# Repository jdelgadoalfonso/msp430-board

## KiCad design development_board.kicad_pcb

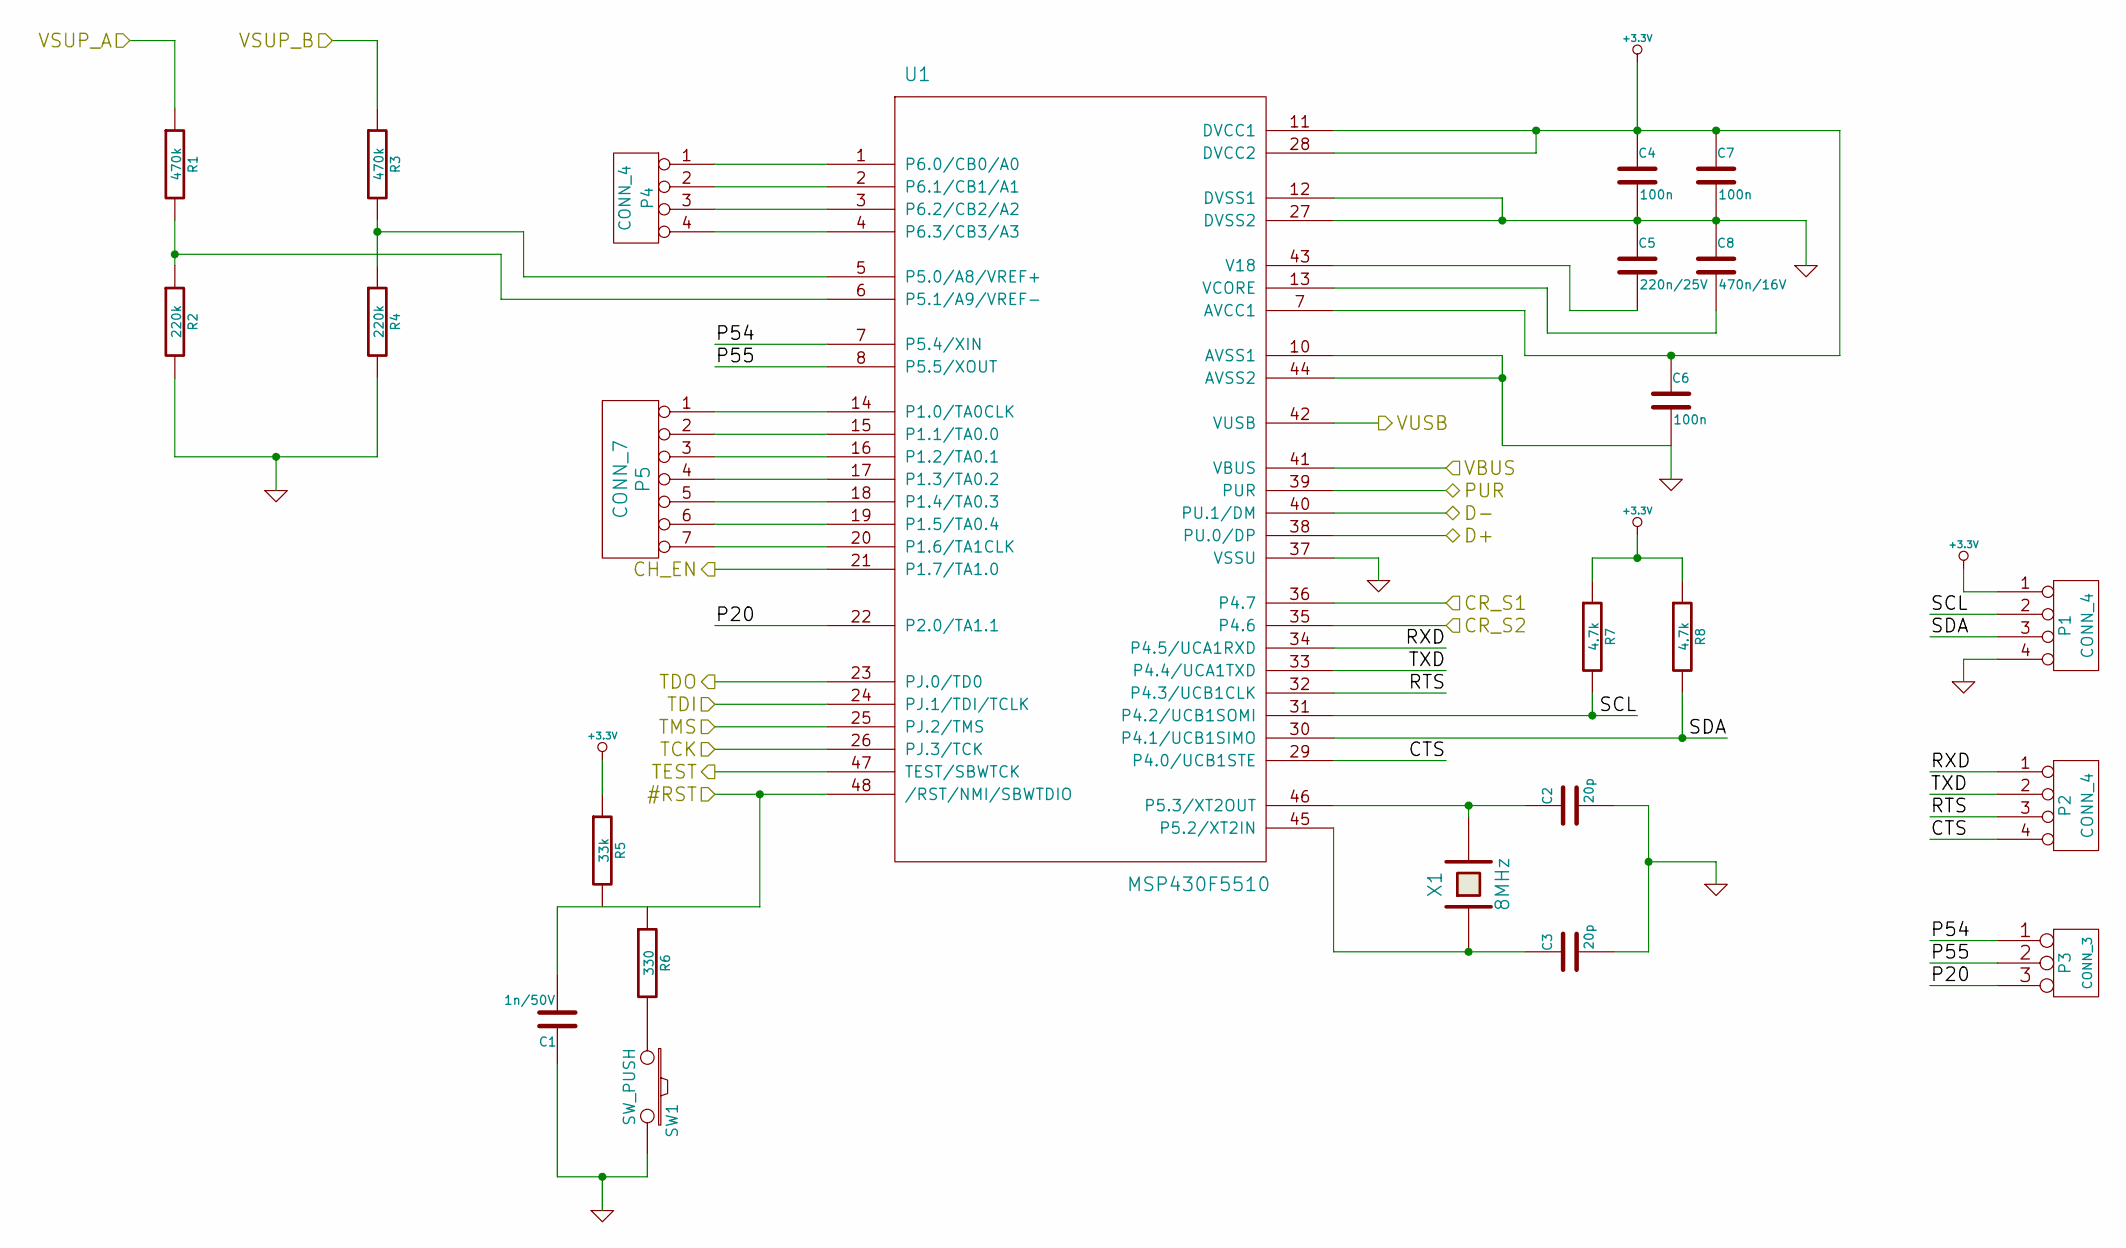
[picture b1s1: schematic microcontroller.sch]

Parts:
C1: 1n/50V
C2, C3: 20p
C4, C6, C7: 100n
C5: 220n/25V
C8: 470n/16V
P1, P2, P4: CONN_4
P3: CONN_3
P5: CONN_7
R1, R3: 470k
R2, R4: 220k
R5: 33k
R6: 330
R7, R8: 4.7k
SW1: SW_PUSH
U1: MSP430F5510
X1: 8MHz

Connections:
+5V: U1.41 (VBUS); also elsewhere on the board
/Debug-Interface/#RST: C1.2, R5.2, R6.1, U1.48 (/RST/NMI/SBWTDIO); also elsewhere on the board
/Debug-Interface/TCK: U1.26 (PJ.3/TCK); also elsewhere on the board
/Debug-Interface/TDI: U1.24 (PJ.1/TDI/TCLK); also elsewhere on the board
/Debug-Interface/TDO: U1.23 (PJ.0/TD0); also elsewhere on the board
/Debug-Interface/TEST: U1.47 (TEST/SBWTCK); also elsewhere on the board
/Debug-Interface/TMS: U1.25 (PJ.2/TMS); also elsewhere on the board
/power/CHR_EN: U1.21 (P1.7/TA1.0); also elsewhere on the board
/power/CR_S1: U1.36 (P4.7); also elsewhere on the board
/power/CR_S2: U1.35 (P4.6); also elsewhere on the board
/power/VSUP_A: R1.1; also elsewhere on the board
/power/VSUP_B: R3.1; also elsewhere on the board
/uController/CTS: P2.4, U1.29 (P4.0/UCB1STE)
/uController/D+: U1.38 (PU.0/DP); also elsewhere on the board
/uController/D-: U1.40 (PU.1/DM); also elsewhere on the board
/uController/P20: P3.3, U1.22 (P2.0/TA1.1)
/uController/PUR: U1.39 (PUR); also elsewhere on the board
/uController/RTS: P2.3, U1.32 (P4.3/UCB1CLK)
/uController/RXD: P2.1, U1.34 (P4.5/UCA1RXD)
/uController/SCL: P1.2, R7.2, U1.31 (P4.2/UCB1SOMI)
/uController/SDA: P1.3, R8.2, U1.30 (P4.1/UCB1SIMO)
/uController/TXD: P2.2, U1.33 (P4.4/UCA1TXD)
/uController/VUSB: U1.42 (VUSB); also elsewhere on the board
GND: C1.1, C2.2, C3.2, C4.2, C5.1, C6.2, C7.2, C8.1, P1.4, R2.2, R4.2, SW1.2, U1.10 (AVSS1), U1.12 (DVSS1), U1.27 (DVSS2), U1.37 (VSSU), U1.44 (AVSS2); also elsewhere on the board
unnamed: P4.3, U1.3 (P6.2/CB2/A2)
unnamed: P4.4, U1.4 (P6.3/CB3/A3)
unnamed: P5.1, U1.14 (P1.0/TA0CLK)
unnamed: P5.2, U1.15 (P1.1/TA0.0)
unnamed: P5.3, U1.16 (P1.2/TA0.1)
unnamed: P5.4, U1.17 (P1.3/TA0.2)
unnamed: P5.5, U1.18 (P1.4/TA0.3)
unnamed: P5.6, U1.19 (P1.5/TA0.4)
unnamed: P5.7, U1.20 (P1.6/TA1CLK)
unnamed: P4.2, U1.2 (P6.1/CB1/A1)
unnamed: P4.1, U1.1 (P6.0/CB0/A0)
unnamed: C2.1, U1.46 (P5.3/XT2OUT), X1.2
unnamed: C8.2, U1.13 (VCORE)
unnamed: C5.2, U1.43 (V18)
unnamed: R1.2, R2.1, U1.6 (P5.1/A9/VREF-)
unnamed: R3.2, R4.1, U1.5 (P5.0/A8/VREF+)
unnamed: C3.1, U1.45 (P5.2/XT2IN), X1.1
unnamed: R6.2, SW1.1

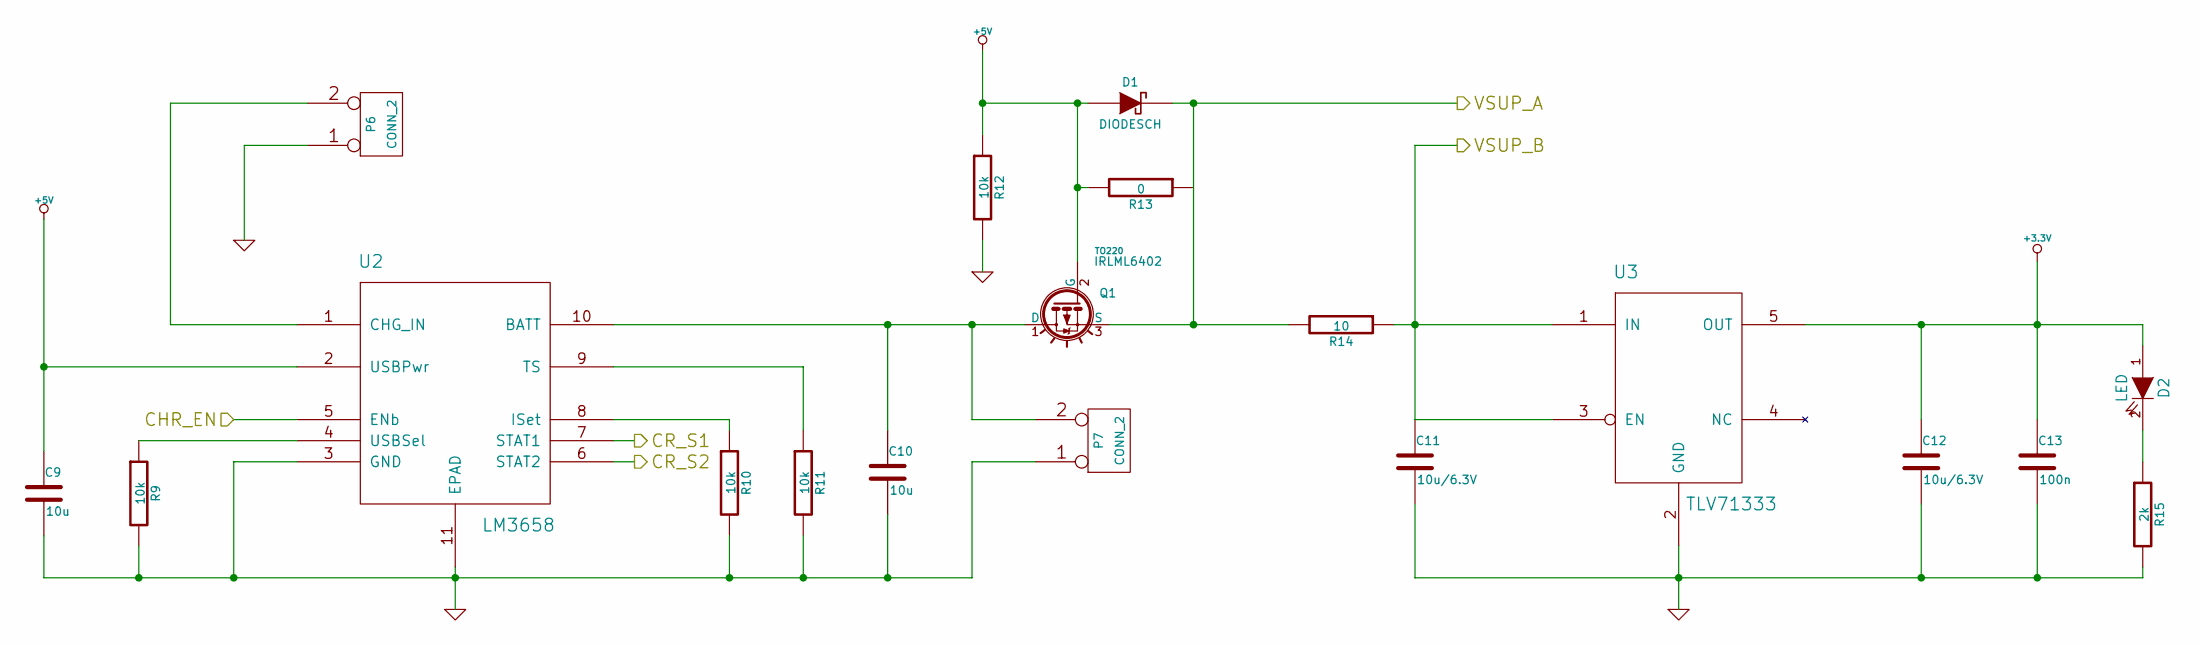
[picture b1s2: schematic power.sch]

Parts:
C9, C10: 10u
C11, C12: 10u/6.3V
C13: 100n
D1: DIODESCH
D2: LED
P6, P7: CONN_2
Q1: IRLML6402; TO220
R9, R10, R11, R12: 10k
R13: 0
R14: 10
R15: 2k
U2: LM3658
U3: TLV71333

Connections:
+5V: C9.1, D1.1 (A), Q1.2 (G), R12.1, R13.2, U2.2 (USBPwr); also elsewhere on the board
/power/CHR_EN: U2.5 (ENb); also elsewhere on the board
/power/CR_S1: U2.7 (STAT1); also elsewhere on the board
/power/CR_S2: U2.6 (STAT2); also elsewhere on the board
/power/VSUP_A: D1.2 (K), Q1.3 (S), R13.1, R14.2; also elsewhere on the board
/power/VSUP_B: C11.1, R14.1, U3.1 (IN), U3.3 (EN); also elsewhere on the board
GND: C9.2, C10.2, C11.2, C12.2, C13.2, P6.1, P7.1, R9.2, R10.2, R11.2, R12.2, R15.2, U2.3 (GND), U2.11 (EPAD), U3.2 (GND); also elsewhere on the board
unnamed: P6.2 (PM), U2.1 (CHG_IN)
unnamed: C10.1, P7.2 (PM), Q1.1 (D), U2.10 (BATT)
unnamed: D2.2 (K), R15.1
unnamed: R10.1, U2.8 (ISet)
unnamed: R9.1, U2.4 (USBSel)
unnamed: R11.1, U2.9 (TS)

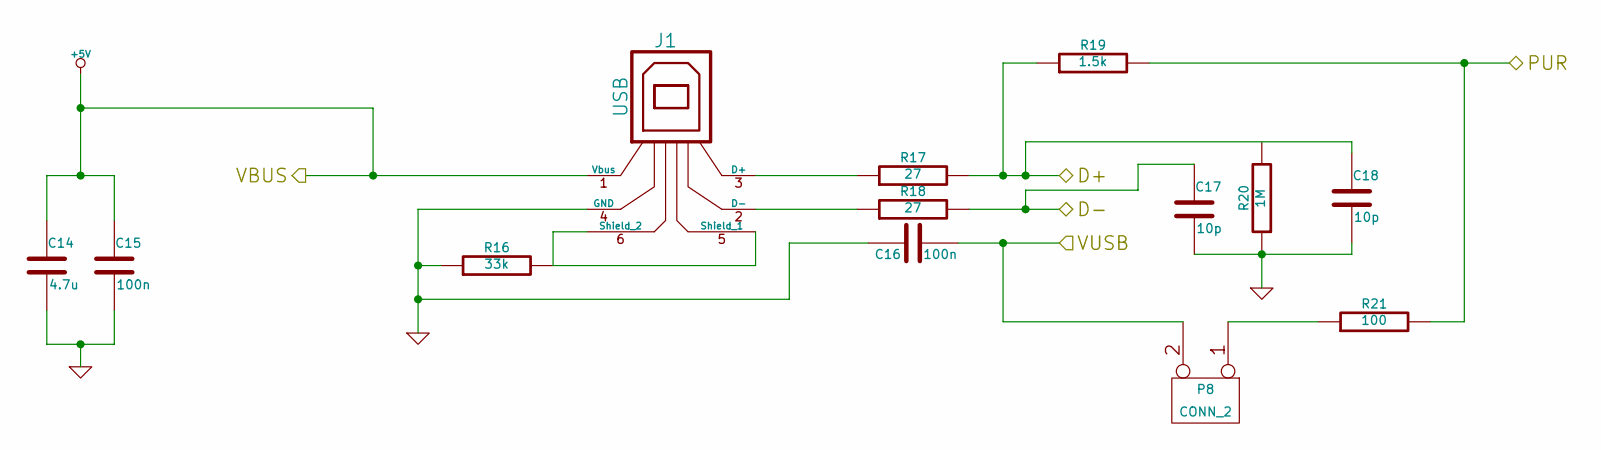
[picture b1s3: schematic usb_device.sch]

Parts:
C14: 4.7u
C15, C16: 100n
C17, C18: 10p
J1: USB
P8: CONN_2
R16: 33k
R17, R18: 27
R19: 1.5k
R20: 1M
R21: 100

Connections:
+5V: C14.1, C15.1, J1.1 (Vbus); also elsewhere on the board
/uController/D+: C18.1, R17.2, R19.1, R20.2; also elsewhere on the board
/uController/D-: C17.1, R18.2; also elsewhere on the board
/uController/PUR: R19.2, R21.2; also elsewhere on the board
/uController/VUSB: C16.2, P8.2 (PM); also elsewhere on the board
GND: C14.2, C15.2, C16.1, C17.2, C18.2, J1.4 (GND), R16.1, R20.1; also elsewhere on the board
unnamed: P8.1, R21.1
unnamed: J1.2 (D-), R18.1
unnamed: J1.3 (D+), R17.1
unnamed: J1.5 (Shield_1), J1.6 (Shield_2), R16.2

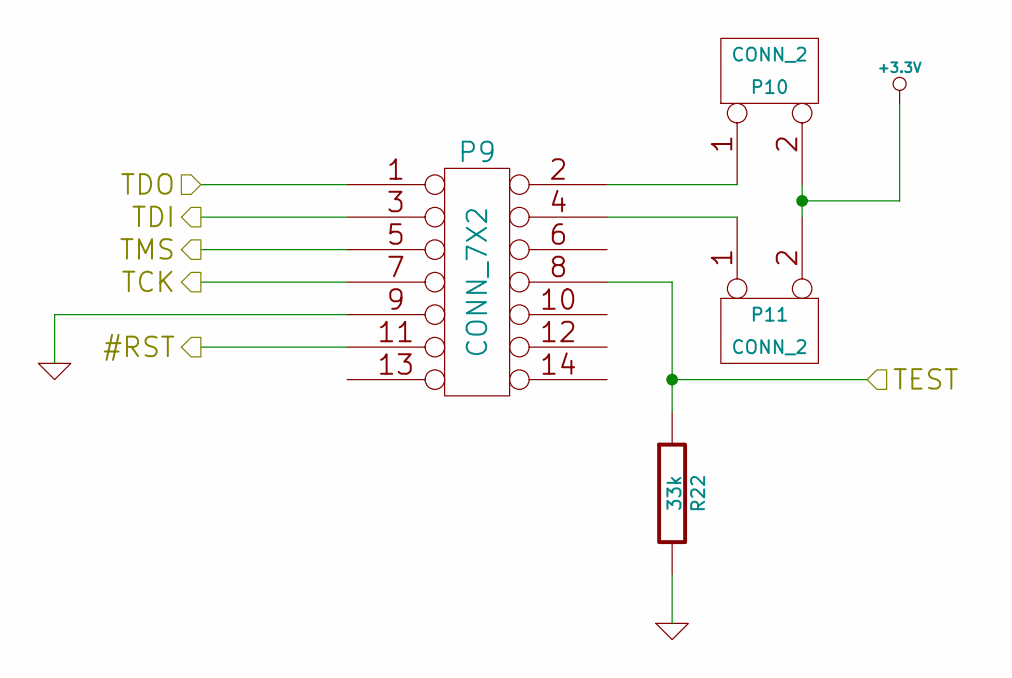
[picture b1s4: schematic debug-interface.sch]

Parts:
P9: CONN_7X2
P10, P11: CONN_2
R22: 33k

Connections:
/Debug-Interface/#RST: P9.11; also elsewhere on the board
/Debug-Interface/TCK: P9.7; also elsewhere on the board
/Debug-Interface/TDI: P9.3; also elsewhere on the board
/Debug-Interface/TDO: P9.1; also elsewhere on the board
/Debug-Interface/TEST: P9.8, R22.1; also elsewhere on the board
/Debug-Interface/TMS: P9.5; also elsewhere on the board
GND: P9.9, R22.2; also elsewhere on the board
unnamed: P9.4, P11.1
unnamed: P9.2, P10.1

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
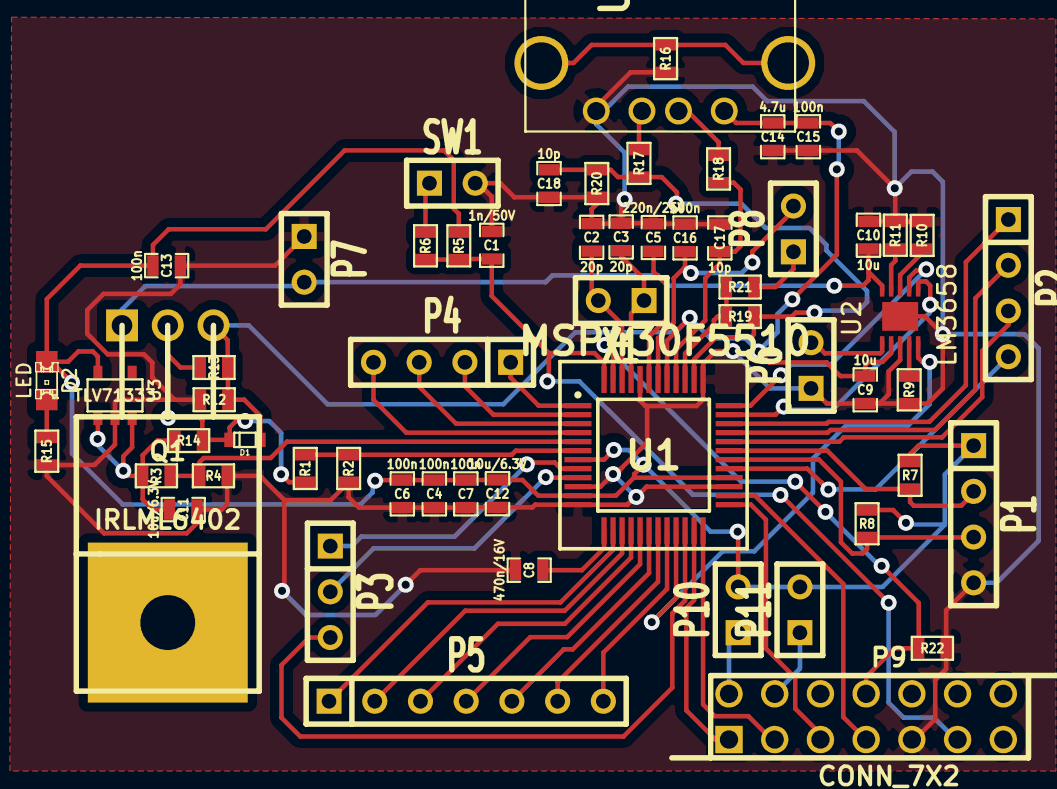
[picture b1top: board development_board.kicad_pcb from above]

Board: 2 copper layers, 60 parts (0 on the bottom side), 57 nets.

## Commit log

2014-02-02 Ignoring files for git
2014-02-02 Adding schematics blocks
2014-02-02 Schematics was finalized
2014-02-02 Adding documentation
2014-02-02 libs
2014-03-15 git config file for gerber diff method
2014-03-20 Annotations were added
2014-03-20 Netlist added
2014-03-20 Linking schematic symbols to layouts
2014-03-20 Updating cache library
2014-06-15 Schotty diode documentation
2014-06-15 schematic was updated
2014-06-15 Crystal oscillator documentation
2014-06-15 Added msp430f5510 footprint
2014-09-13 Assosiation of crystal and button
2014-09-13 Adding library for lm3568
2014-11-09 Adding module LM3658
2014-11-09 Adding PCB
2014-11-09 Modification of LM3568 module
2014-11-09 Modification of MSP430 module
2014-11-09 Ignoring backup files
2014-11-09 Fixing some errors
2014-11-09 Ignoring binary files
2014-11-09 Adding software
